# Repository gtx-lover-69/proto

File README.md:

# Proto!

Proto is a tiny handheld games console based on the Raspberry Pi Pico 2W. I chose the wireless connectivity version for bluetooth support.

It has a full colour LCD, 8 buttons in the form of 2 d-pads on each side, and semi-stereo speakers near the middle.
Proto also features a USB-C port for charging (with a dedicated RGB LED), a 3.5mm headphone jack, and a Micro SD card slot.

You can view the 3d model [here](https://3dviewer.net/#model=https://github.com/gtx-lover-69/proto/blob/main/proto.step)

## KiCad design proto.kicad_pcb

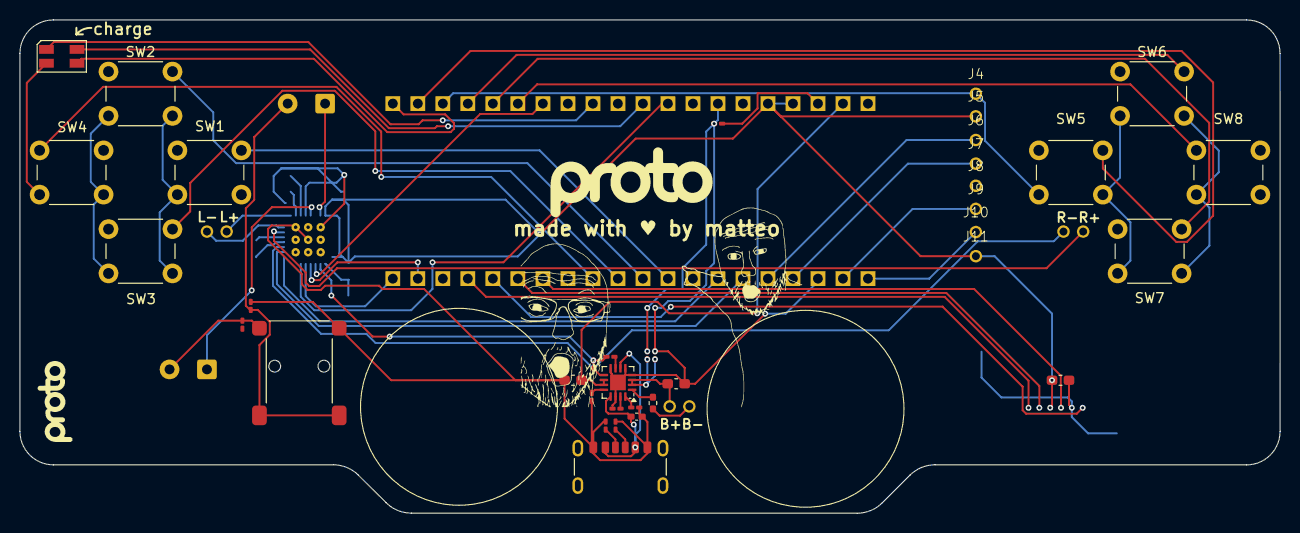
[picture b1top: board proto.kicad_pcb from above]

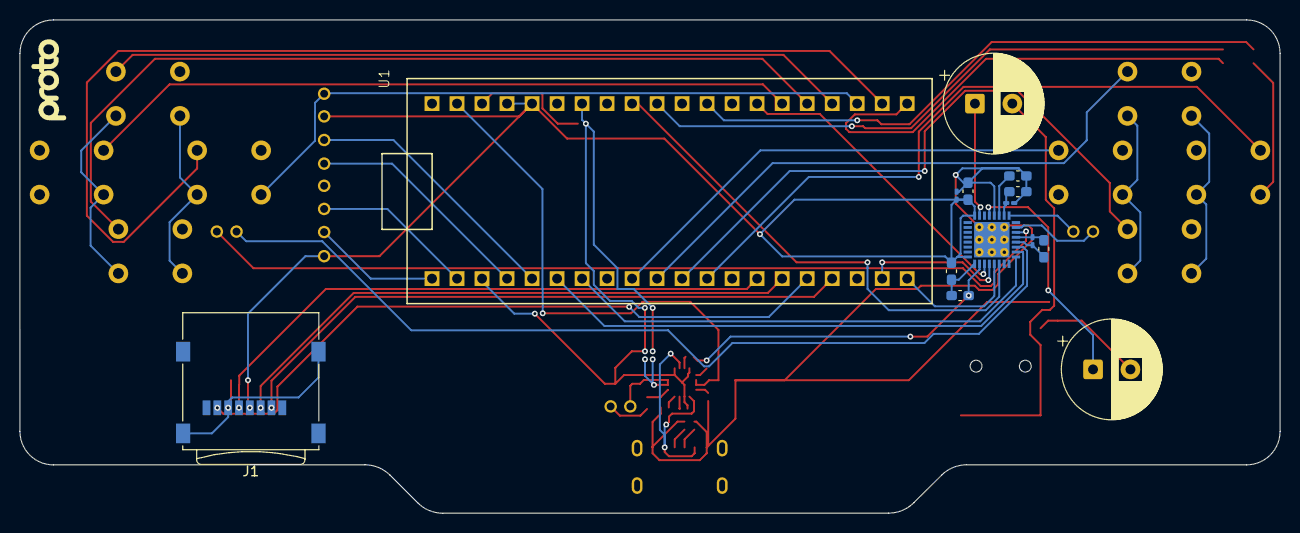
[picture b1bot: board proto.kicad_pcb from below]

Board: 2 copper layers, 128.0 x 50.1 mm, 57 parts (14 on the bottom side), 26 nets.

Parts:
C1, C2, C6, C10, C11, C12: 10uF; C_0603_1608Metric_Pad1.08x0.95mm_HandSolder
C3, C8, C9: 4.7uF; C_0603_1608Metric_Pad1.08x0.95mm_HandSolder
C4, C5: 220uF; CP_Radial_D10.0mm_P3.80mm
C7: 1uF; C_0402_1005Metric_Pad0.74x0.62mm_HandSolder
C13, C14, C15: 0.1uF; C_0201_0603Metric_Pad0.64x0.40mm_HandSolder
C16: 100nF; C_0201_0603Metric_Pad0.64x0.40mm_HandSolder
D1: LED_RGBA; LED_RGB_Wuerth-PLCC4_3.2x2.8mm_150141M173100
IC1: WM8960CGEFL_V; QFN50P500X500X100-33N
J1: Micro_SD_Card; microSD_HC_Wuerth_693072010801
J2: AudioJack3; Jack_3.5mm_Lumberg_1503_02_Horizontal
J3: USB_C_Receptacle_PowerOnly_6P; USB_C_Receptacle_GCT_USB4125-xx-x-0190_6P_TopMnt_Horizontal
J4: GND; Untitled
J5: VCC; Untitled
J6: SCL; Untitled
J7: SDA; Untitled
J8: RES; Untitled
J9: DC; Untitled
J10: CS; Untitled
J11: BL; Untitled
J12: BAT+; Untitled
J13: BAT-; Untitled
J14: L-; Untitled
J15: L+; Untitled
J16: R-; Untitled
J17: R+; Untitled
R1, R2: 5.1k; R_0201_0603Metric_Pad0.64x0.40mm_HandSolder
R3: 2k; R_0201_0603Metric_Pad0.64x0.40mm_HandSolder
R4: 8k; R_0201_0603Metric_Pad0.64x0.40mm_HandSolder
R5: 1.5k; R_0201_0603Metric_Pad0.64x0.40mm_HandSolder
R6, R7, R8, R9: 10k; R_0201_0603Metric_Pad0.64x0.40mm_HandSolder
R10, R11: 1M; R_0201_0603Metric_Pad0.64x0.40mm_HandSolder
SW1, SW2, SW3, SW4, SW5, SW6, SW7, SW8: SW_Push; SW_PUSH_6mm
TH1: Thermistor; R_0402_1005Metric_Pad0.72x0.64mm_HandSolder
U1: Raspberrypi pico2 THT
U2: BQ24074RGT; VQFN-16-1EP_3x3mm_P0.5mm_EP1.6x1.6mm

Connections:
+3.3V: C1.1, C2.1, C6.1, C10.2, C13.2, IC1.8 (DCVDD), IC1.10 (DBVDD), IC1.32 (AVDD), J1.4 (VDD), J5.1 (Pin_1_1), J11.1 (Pin_1_1), R6.2, R7.1
+5V: C11.2, C12.2, C14.2, C15.2, IC1.21 (SPKVDD2), IC1.26 (SPKVDD1), U2.6 (EN1)
BAT+: C1.2, C2.2, C3.2, C6.2, C7.2, C8.2, C9.1, C9.2, C10.1, C11.1, C12.1, C13.1, C14.1, C15.1, C16.1, C16.2, D1.4 (A), IC1.9 (DGND), IC1.20 (SPKGND2), IC1.24 (SPKGND1), IC1.28 (AGND), IC1.33 (GND_PADDLE), IC1.P$1 (GND_PADDLE), IC1.P$2 (GND_PADDLE), IC1.P$3 (GND_PADDLE), IC1.P$4 (GND_PADDLE), IC1.P$5 (GND_PADDLE), IC1.P$6 (GND_PADDLE), IC1.P$7 (GND_PADDLE), IC1.P$8 (GND_PADDLE), IC1.P$9 (GND_PADDLE), J1.6 (VSS), J1.SH (SHIELD), J2.S, J3.A12 (GND), J3.B12 (GND), J3.SH (SHIELD), J4.1 (Pin_1_1), J12.1 (Pin_1_1), R1.1, R2.1, R3.2, R4.2, R5.2, R8.1, R9.1, R10.1, R10.2, R11.1, R11.2, SW1.2, SW2.2, SW3.2, SW4.2, SW5.2, SW6.2, SW7.2, SW8.2, U1.GND, U1.GP28_A2, U2.2 (BAT), U2.3 (BAT), U2.4 (~CE), U2.5 (EN2), U2.8 (VSS), U2.14 (TMR), U2.17 (VSS)
BAT-: J13.1 (Pin_1_1), TH1.1
BLCK: IC1.12 (BCLK), U1.GP14
CS: J1.2 (DAT3/CD), J10.1 (Pin_1_1)
DACDAT: IC1.14 (DACDAT), U1.GP27_A1
unnamed: C4.2, J2.R, R9.2
unnamed: C5.2, J2.T, R8.2
unnamed: C5.1, IC1.31 (HP_L)
unnamed: C4.1, IC1.29 (HP_R)
unnamed: IC1.23 (SPK_LN), J14.1 (Pin_1_1)
unnamed: IC1.25 (SPK_LP), J15.1 (Pin_1_1)
unnamed: IC1.19 (SPK_RN), J16.1 (Pin_1_1)
unnamed: IC1.22 (SPK_RP), J17.1 (Pin_1_1)
unnamed: C3.1, IC1.27 (VMID)
unnamed: J3.A5 (CC1), R2.2
unnamed: J3.B5 (CC2), R1.2
unnamed: R5.1, U2.12 (ILIM)
unnamed: C7.1, J3.A9 (VBUS), J3.B9 (VBUS), U2.13 (IN)
unnamed: R3.1, U2.16 (ISET)
unnamed: R4.1, U2.15 (ITERM)
unnamed: R6.1, U2.9 (~CHG)
unnamed: R7.2, U2.7 (~PGOOD)
TS: TH1.2, U2.1 (TS)
VSYS: C8.1, U2.10 (OUT), U2.11 (OUT)
